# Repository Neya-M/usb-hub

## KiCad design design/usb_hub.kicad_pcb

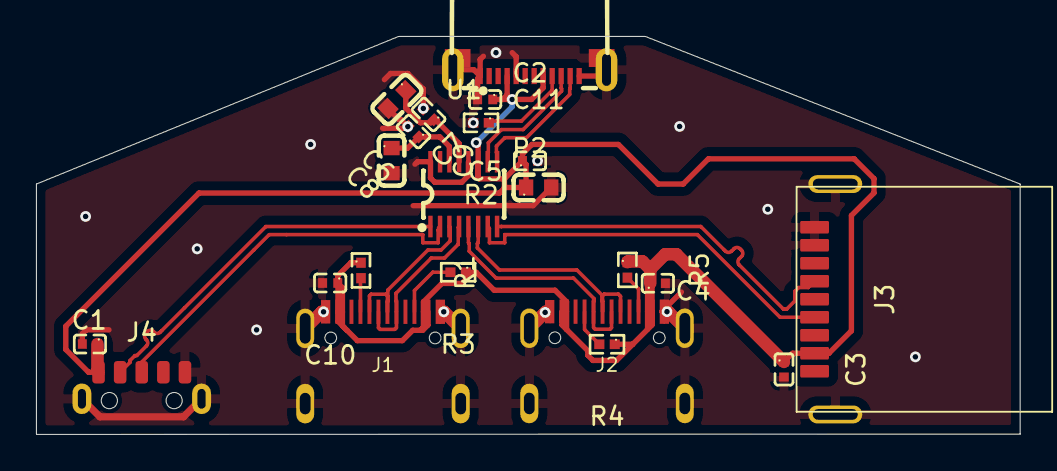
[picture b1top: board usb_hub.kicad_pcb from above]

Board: 2 copper layers, 54.7 x 22.1 mm, 22 parts (0 on the bottom side), 19 nets.

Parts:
C1, C2, C3, C4, C5, C6, C8, C10: 1uF; C0402
C7, C9, C11: 100nF; C0603
J1, J2: USB_C_Receptacle_USB2.0_14P; TYPE-C-31-M-12
J3: USB_A; U-A-39DS-Y-1
J4: USB_B_Micro; MICRO-ZD-102PWB
P2: USB_C_Plug_USB2.0; USB-C-SMD_U261-121N-4BS2S
R1, R3, R4, R5: 56k; R0402
R2: 5.1K; R0402
U1: SL2.1S; SSOP-16_L4.6-W2.6-P0.53-LS4.0-BL

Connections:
1DN: J3.2 (D-), U1.7 (DM1)
1DP: J3.3 (D+), U1.8 (DP1)
2DN: J2.A7 (D-), J2.B7 (D-), U1.5 (DM2)
2DP: J2.A6 (D+), J2.B6 (D+), U1.6 (DP2)
3DN: J1.A7 (D-), J1.B7 (D-), U1.3 (DM3)
3DP: J1.A6 (D+), J1.B6 (D+), U1.4 (DP3)
4DN: J4.2 (D-), U1.1 (DM4)
4DP: J4.3 (D+), U1.2 (DP4)
+5V: C1.1, C2.1, C3.1, C4.1, C5.1, C10.1, C11.1, J1.A4 (VBUS), J1.A9 (VBUS), J1.B4 (VBUS), J1.B9 (VBUS), J2.A4 (VBUS), J2.A9 (VBUS), J2.B4 (VBUS), J2.B9 (VBUS), J3.1 (VBUS), J4.1 (VBUS), P2.A4 (VBUS), P2.B9 (VBUS), R1.1, R3.1, R4.1, R5.1, U1.11 (VDD5)
D+: P2.A6 (D+), U1.10 (UDP)
D-: P2.A7 (D-), U1.9 (UDM)
GND: C1.2, C2.2, C3.2, C4.2, C5.2, C6.2, C7.2, C8.2, C9.2, C10.2, C11.2, J1.A1 (GND), J1.A12 (GND), J1.B1 (GND), J1.B12 (GND), J1.S1 (SHIELD), J2.A1 (GND), J2.A12 (GND), J2.B1 (GND), J2.B12 (GND), J2.S1 (SHIELD), J3.4 (GND), J3.5 (Shield), J4.5 (GND), J4.6 (Shield), P2.A1 (GND), P2.A12 (GND), P2.B12 (GND), P2.S1 (SHIELD), R2.2, U1.12 (VSS), U1.16 (XIN)
unnamed: J1.A5 (CC1), R1.2
unnamed: J1.B5 (CC2), R3.2
unnamed: J2.A5 (CC1), R4.2
unnamed: J2.B5 (CC2), R5.2
unnamed: P2.A5 (CC), R2.1
unnamed: C8.1, C9.1, U1.14 (VDD18)
unnamed: C6.1, C7.1, U1.13 (VDD33)

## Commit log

2026-06-25 initial
2026-06-25 update 2
2026-06-26 add case
2026-06-26 update boms
